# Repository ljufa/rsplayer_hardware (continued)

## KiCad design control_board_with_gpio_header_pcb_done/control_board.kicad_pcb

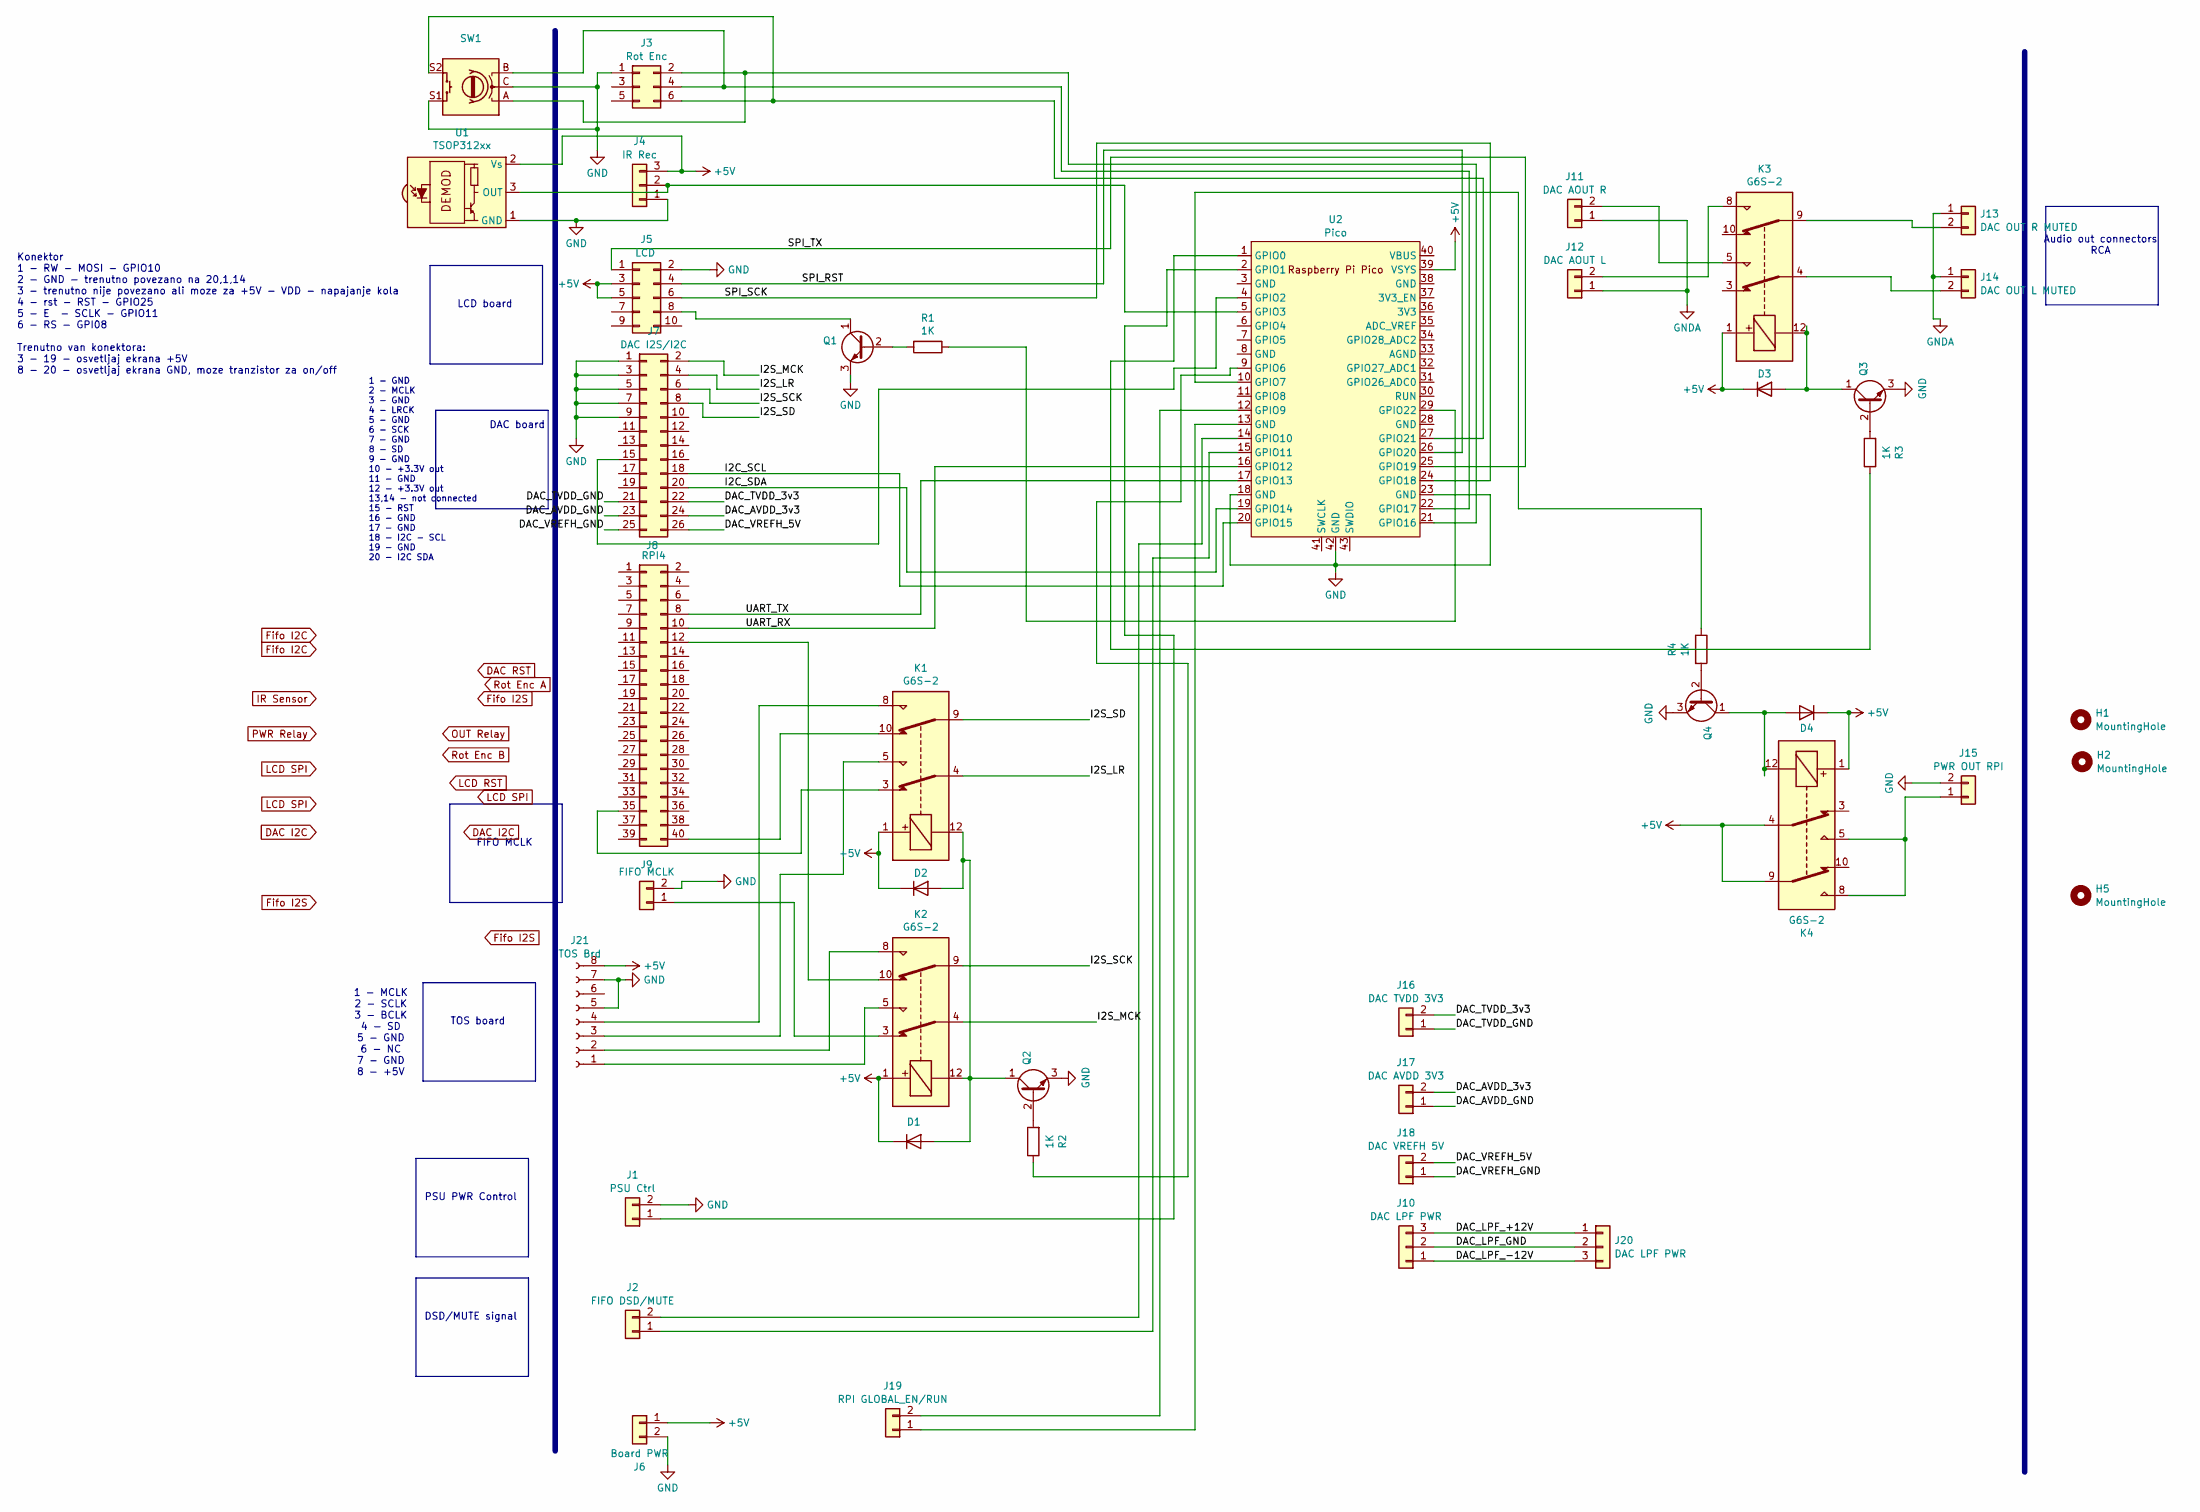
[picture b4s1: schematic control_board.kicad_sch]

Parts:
D1, D2, D3, D4: 1N4004; D_MELF
H1, H2, H5: MountingHole; MountingHole_3.2mm_M3
J1: PSU Ctrl; PinHeader_1x02_P2.54mm_Vertical
J2: FIFO DSD/MUTE; PinHeader_1x02_P2.54mm_Vertical
J3: Rot Enc; IDC-Header_2x03_P2.54mm_Vertical
J4: IR Rec; PinHeader_1x03_P2.54mm_Vertical
J5: LCD; IDC-Header_2x05_P2.54mm_Vertical
J6: Board PWR; TerminalBlock_Philmore_TB132_1x02_P5.00mm_Horizontal
J7: DAC I2S/I2C; diyinkhak4497board
J8: RPI4; PinHeader_2x20_P2.54mm_Vertical
J9: FIFO MCLK; PinHeader_1x02_P2.54mm_Vertical
J10: DAC LPF PWR; TerminalBlock_Philmore_TB133_1x03_P5.00mm_Horizontal
J11: DAC AOUT R; PinHeader_1x02_P2.54mm_Vertical
J12: DAC AOUT L; PinHeader_1x02_P2.54mm_Vertical
J13: DAC OUT R MUTED; PinHeader_1x02_P2.54mm_Vertical
J14: DAC OUT L MUTED; PinHeader_1x02_P2.54mm_Vertical
J15: PWR OUT RPI; TerminalBlock_Philmore_TB132_1x02_P5.00mm_Horizontal
J16: DAC TVDD 3V3; TerminalBlock_Philmore_TB132_1x02_P5.00mm_Horizontal
J17: DAC AVDD 3V3; TerminalBlock_Philmore_TB132_1x02_P5.00mm_Horizontal
J18: DAC VREFH 5V; TerminalBlock_Philmore_TB132_1x02_P5.00mm_Horizontal
J19: RPI GLOBAL_EN/RUN; PinHeader_1x02_P2.54mm_Vertical
J20: DAC LPF PWR; PinSocket_1x03_P2.54mm_Vertical
J21: TOS Brd; tosInputBoard
K1, K2, K3, K4: G6S-2; Relay_DPDT_Omron_G6S-2
Q1, Q2, Q3, Q4: BC547; TO-92_Inline
R1, R2, R3, R4: 1K; R_1206_3216Metric_Pad1.30x1.75mm_HandSolder
SW1: RotaryEncoder_Switch
U1: TSOP312xx; Vishay_CAST-3Pin
U2: Pico; RaspberryPi_Pico_Common_THT

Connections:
+5V: D1.1 (K), D2.1 (K), D3.1 (K), D4.1 (K), J4.3, J5.3, J5.5, J6.1, J21.8, K1.1, K2.1, K3.1, K4.1, K4.4, K4.9, U2.39 (VSYS)
/DAC_AVDD_3v3: J7.24, J17.2
/DAC_AVDD_GND: J7.23, J17.1
/DAC_LPF_+12V: J10.3, J20.1
/DAC_LPF_-12V: J10.1, J20.3
/DAC_LPF_GND: J10.2, J20.2
/DAC_TVDD_3v3: J7.22, J16.2
/DAC_TVDD_GND: J7.21, J16.1
/DAC_VREFH_5V: J7.26, J18.2
/DAC_VREFH_GND: J7.25, J18.1
/I2C_SCL: J7.18, U2.20 (GPIO15)
/I2C_SDA: J7.20, U2.19 (GPIO14)
/I2S_LR: J7.4, K1.4
/I2S_MCK: J7.2, K2.4
/I2S_SCK: J7.6, K2.9
/I2S_SD: J7.8, K1.9
/SPI_RST: J5.4, U2.26 (GPIO20)
/SPI_SCK: J5.6, U2.24 (GPIO18)
/SPI_TX: J5.1, U2.25 (GPIO19)
/UART_RX: J8.10, U2.16 (GPIO12)
/UART_TX: J8.8, U2.17 (GPIO13)
GND: J1.2, J3.1, J4.1, J5.2, J6.2, J7.1, J7.3, J7.5, J7.7, J7.9, J9.2, J15.2, J21.5, J21.7, Q1.3 (E), Q2.3 (E), Q3.3 (E), Q4.3 (E), U2.18 (GND), U2.23 (GND), U2.42 (GND)
GNDA: J11.1, J12.1, J13.1, J14.1
unnamed: D1.2 (A), D2.2 (A), K1.12, K2.12, Q2.1 (C)
unnamed: D3.2 (A), K3.12, Q3.1 (C)
unnamed: D4.2 (A), K4.12, Q4.1 (C)
unnamed: J1.1, U2.2 (GPIO1)
unnamed: J2.1, U2.15 (GPIO11)
unnamed: J2.2, U2.14 (GPIO10)
unnamed: J3.2, U2.21 (GPIO16)
unnamed: J3.4, U2.22 (GPIO17)
unnamed: J3.6, U2.27 (GPIO21)
unnamed: J4.2, U2.5 (GPIO3)
unnamed: J5.8, Q1.1 (C)
unnamed: J7.15, U2.4 (GPIO2)
unnamed: J8.12, K2.10
unnamed: J8.35, K1.3
unnamed: J8.40, K1.10
unnamed: J9.1, K2.3
unnamed: J11.2, K3.5
unnamed: J12.2, K3.8
unnamed: J13.2, K3.9
unnamed: J14.2, K3.4
unnamed: J15.1, K4.5, K4.8
unnamed: J19.1, U2.13 (GND)
unnamed: J19.2, U2.12 (GPIO9)
unnamed: J21.1, K2.5
unnamed: J21.2, K2.8
unnamed: J21.3, K1.5
unnamed: J21.4, K1.8
unnamed: Q1.2 (B), R1.2
unnamed: Q2.2 (B), R2.2
unnamed: Q3.2 (B), R3.2
unnamed: Q4.2 (B), R4.2
unnamed: R3.1, U2.1 (GPIO0)
unnamed: R2.1, U2.9 (GPIO6)
unnamed: R4.1, U2.10 (GPIO7)
unnamed: R1.1, U2.29 (GPIO22)

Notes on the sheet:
FIFO MCLK
Audio out connectors RCA
Konektor 1 - RW - MOSI - GPIO10 2 - GND - trenutno povezano na 20,1,14 3 - trenutno nije povezano ali moze za +5V - VDD - napajanje kola 4 - rst - RST - GPIO25 5 - E - SCLK - GPIO11 6 - RS - GPI08 Trenutno van konektora: 3 - 19 - osvetljaj ekrana +5V 8 - 20 - osvetljaj ekrana GND, moze tranzistor z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
DAC board
LCD board
PSU PWR Control
DSD/MUTE signal
1 - GND 2 - MCLK 3 - GND 4 - LRCK 5 - GND 6 - SCK 7 - GND 8 - SD 9 - GND 10 - +3.3V out 11 - GND 12 - +3.3V out 13,14 - not connected 15 - RST 16 - GND 17 - GND 18 - I2C - SCL 19 - GND 20 - I2C SDA
1 - MCLK 2 - SCLK 3 - BCLK 4 - SD 5 - GND 6 - NC 7 - GND 8 - +5V
TOS board

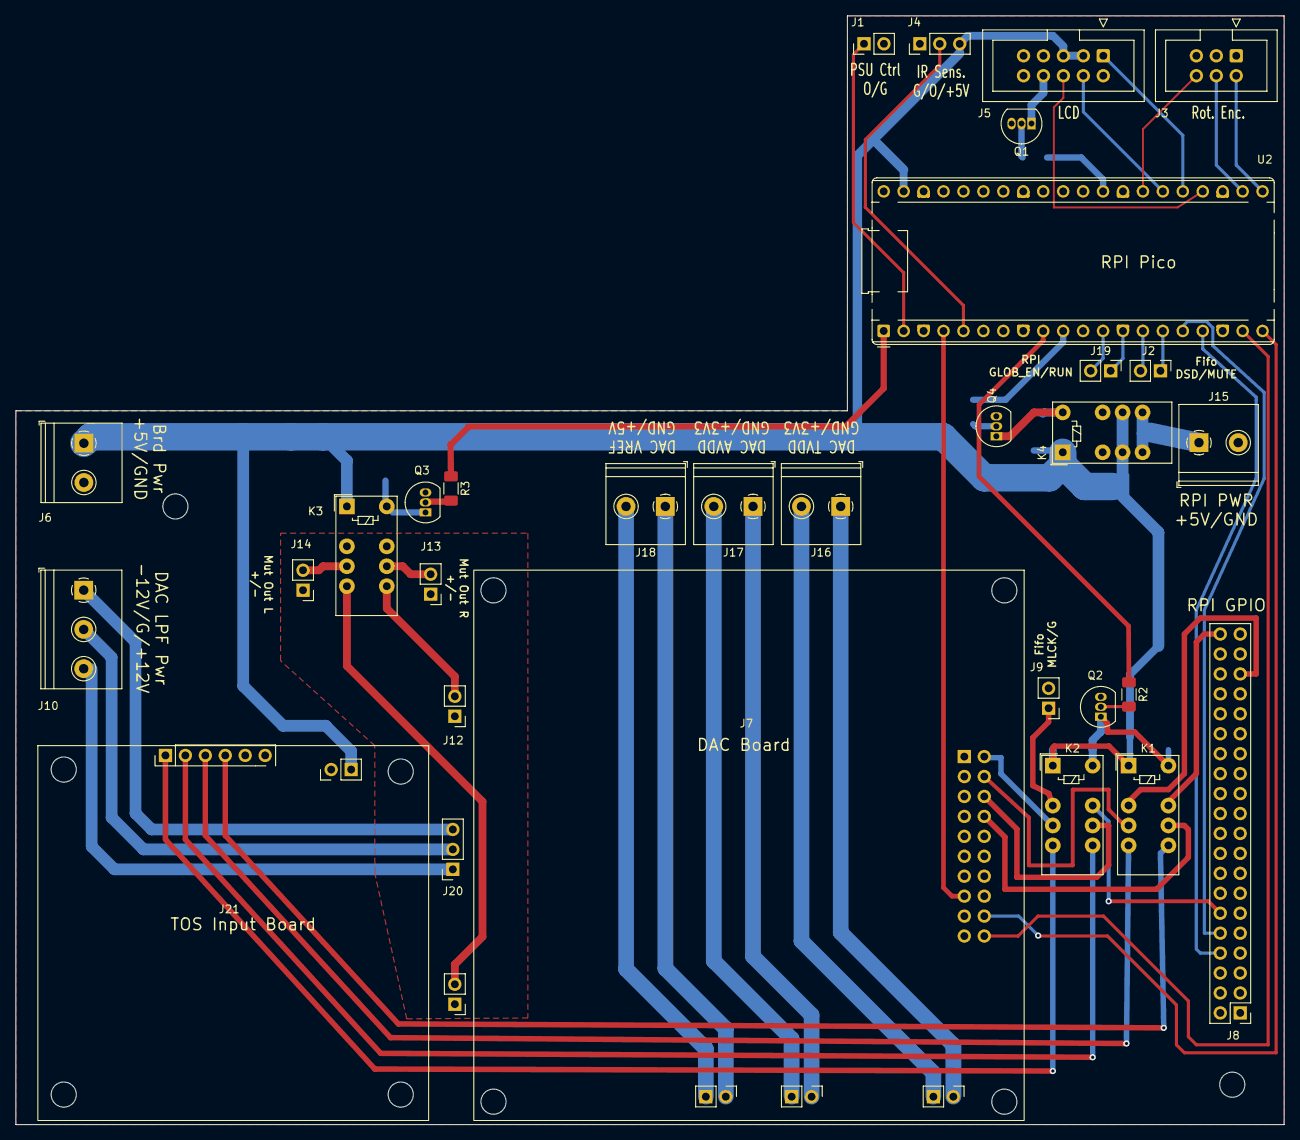
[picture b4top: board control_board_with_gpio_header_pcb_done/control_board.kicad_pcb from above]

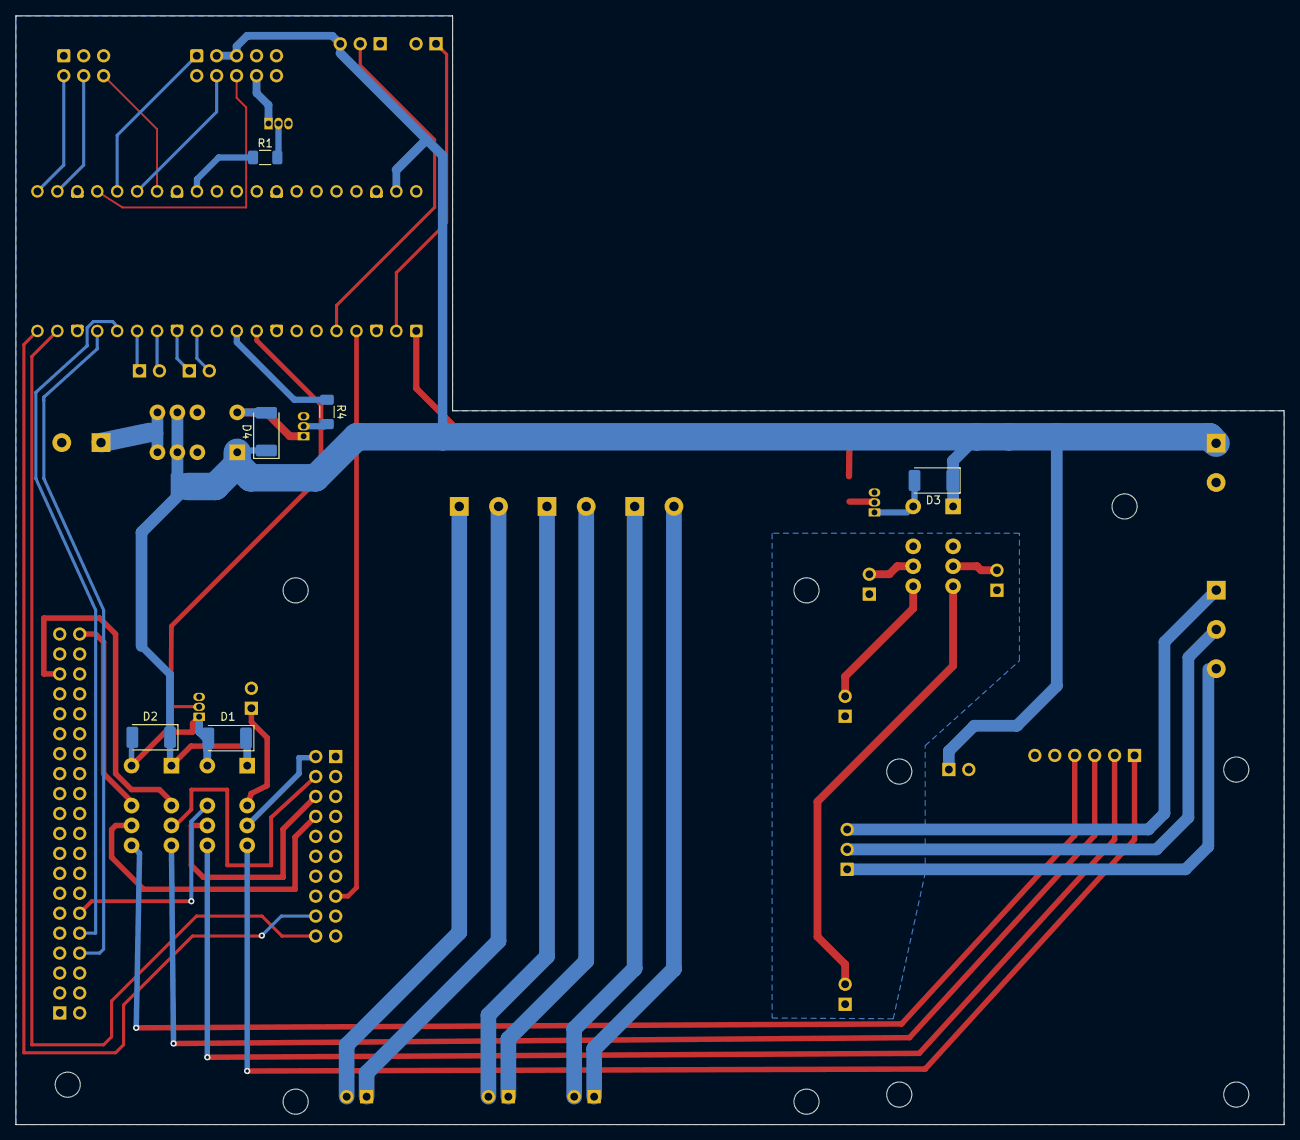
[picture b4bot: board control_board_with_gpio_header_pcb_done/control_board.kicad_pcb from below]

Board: 2 copper layers, 161.5 x 141.2 mm, 41 parts (6 on the bottom side), 58 nets.

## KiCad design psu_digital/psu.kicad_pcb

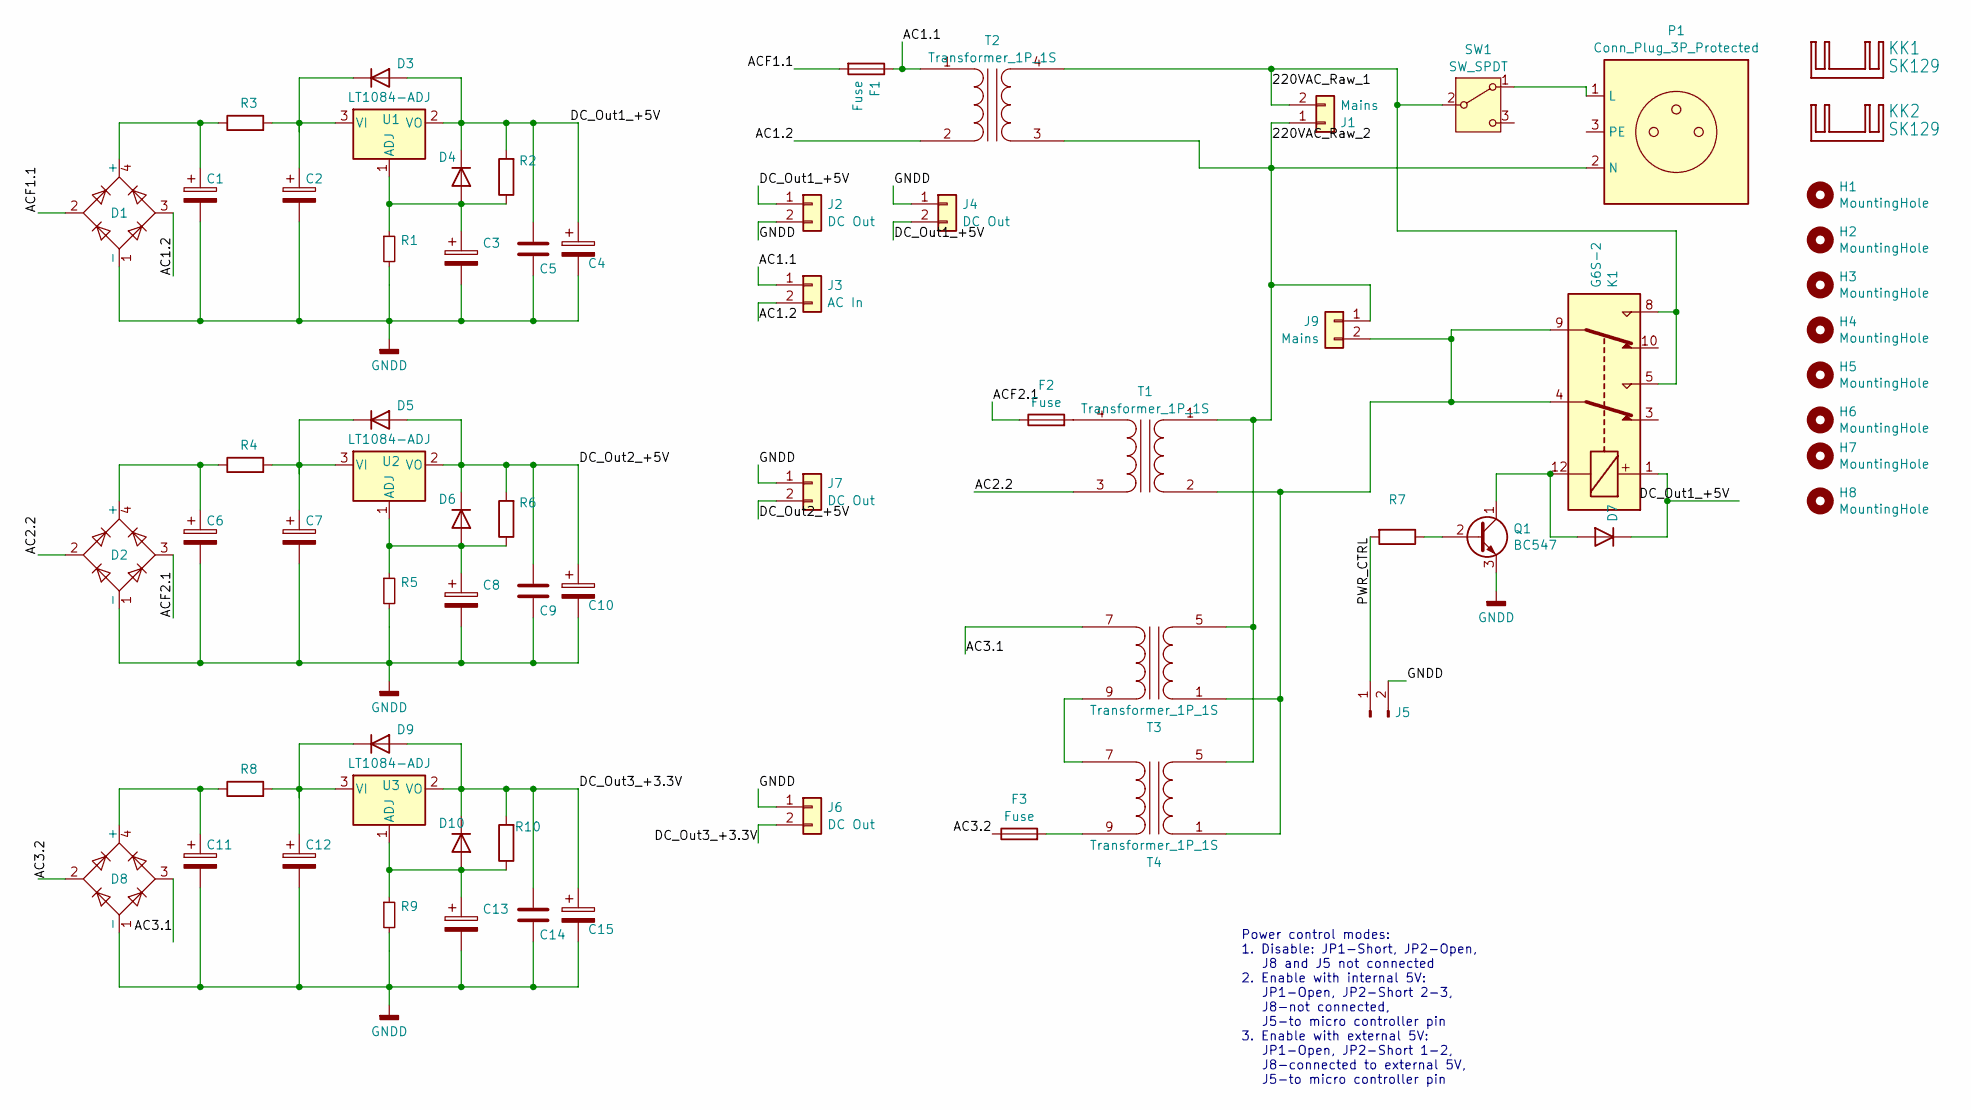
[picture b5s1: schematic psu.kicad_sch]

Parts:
C1, C2: 2200uF/40v; CP_Axial_L42.0mm_D26.0mm_P45.00mm_Horizontal
C3, C8, C13: 10uF/35V; CP_Radial_D5.0mm_P2.00mm
C4, C10, C15: 220uF; CP_Radial_D10.0mm_P5.00mm
C5, C9, C14: 1uF; C_Rect_L10.0mm_W2.5mm_P7.50mm_MKS4
C6, C7, C11, C12: 2200uF/40v; CP_Radial_D13.0mm_P5.00mm
D1, D2, D8: B80C3x00-2200A; Diode_Bridge_32.0x5.6x17.0mm_P10.0mm_P7.5mm
D3, D4, D5, D6, D9, D10: 1N4004; D_DO-41_SOD81_P10.16mm_Horizontal
D7: 1N4004; D_A-405_P7.62mm_Horizontal
F1, F2, F3: Fuse; SH22,5A
H1, H2, H5, H6, H7, H8: MountingHole; MountingHole_3.2mm_M3
H3, H4: MountingHole; MountingHole_3.2mm_M3_Pad_Via
J1, J9: Mains; TerminalBlock_Philmore_TB132_1x02_P5.00mm_Horizontal
J2, J4, J6, J7: DC Out; TerminalBlock_Philmore_TB132_1x02_P5.00mm_Horizontal
J3: AC In; TerminalBlock_Philmore_TB132_1x02_P5.00mm_Horizontal
J5: Conn_01x02_Pin; JST_EH_B2B-EH-A_1x02_P2.50mm_Vertical
K1: G6S-2; Relay_DPDT_Omron_G6S-2
KK1, KK2: SK129; Heatsink_Fischer_SK104-STCB_35x13mm__2xDrill3.5mm_ScrewM3
P1: Conn_Plug_3P_Protected
Q1: BC547; TO-92_Inline
R1, R5, R9: 82R; R_Axial_DIN0207_L6.3mm_D2.5mm_P10.16mm_Horizontal
R2, R6, R10: 330; R_Axial_DIN0207_L6.3mm_D2.5mm_P10.16mm_Horizontal
R3, R4, R8: 2.2; R_Axial_DIN0617_L17.0mm_D6.0mm_P20.32mm_Horizontal
R7: 1k; R_Axial_DIN0207_L6.3mm_D2.5mm_P2.54mm_Vertical
SW1: SW_SPDT
T1: Transformer_1P_1S; MYRRA_44266
T2: Transformer_1P_1S
T3, T4: Transformer_1P_1S; Transformer_Breve_TEZ-35x42_crni_6v_3.va
U1, U2, U3: LT1084-ADJ; TO-220-3_Vertical

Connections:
/220VAC_Raw_1: J1.2, K1.5, K1.8, SW1.2 (B), T2.4 (SB)
/220VAC_Raw_2: J1.1, J9.1, P1.2 (N), T1.1 (AA), T2.3 (SA), T3.5 (AB), T4.5 (AB)
/AC1.1: F1.1, J3.1, T2.1 (AA)
/AC1.2: D1.3, J3.2, T2.2 (AB)
/AC2.2: D2.2, T1.3 (SA)
/AC3.1: D8.3, T3.7 (SA)
/AC3.2: D8.2, F3.1
/ACF1.1: D1.2, F1.2
/ACF2.1: D2.3, F2.1
/DC_Out1_+5V: C4.1, C5.1, D3.2 (A), D4.1 (K), D7.1 (K), J2.1, J4.2, K1.1, R2.2, U1.2 (VO)
/DC_Out2_+5V: C9.1, C10.1, D5.2 (A), D6.1 (K), J7.2, R6.2, U2.2 (VO)
/DC_Out3_+3.3V: C14.1, C15.1, D9.2 (A), D10.1 (K), J6.2, R10.2, U3.2 (VO)
/PWR_CTRL: J5.1, R7.2
GNDD: C1.2, C2.2, C3.2, C4.2, C5.2, C6.2, C7.2, C8.2, C9.2, C10.2, C11.2, C12.2, C13.2, C14.2, C15.2, D1.1 (-), D2.1 (-), D8.1 (-), J2.2, J4.1, J5.2, J6.1, J7.1, Q1.3 (E), R1.2, R5.2, R9.2
unnamed 14: C1.1, D1.4 (+), R3.1; also elsewhere on the board
unnamed: C6.1, D2.4 (+), R4.1
unnamed 16: C2.1, D3.1 (K), R3.2, U1.3 (VI); also elsewhere on the board
unnamed: C3.1, D4.2 (A), R1.1, R2.1, U1.1 (ADJ)
unnamed: C7.1, D5.1 (K), R4.2, U2.3 (VI)
unnamed: C8.1, D6.2 (A), R5.1, R6.1, U2.1 (ADJ)
unnamed: D7.2 (A), K1.12, Q1.1 (C)
unnamed: C11.1, D8.4 (+), R8.1
unnamed: C12.1, D9.1 (K), R8.2, U3.3 (VI)
unnamed: C13.1, D10.2 (A), R9.1, R10.1, U3.1 (ADJ)
unnamed: J9.2, K1.4, K1.9, T1.2 (AB), T3.1 (AA), T4.1 (AA)
unnamed: P1.1 (L), SW1.1 (A)
unnamed: Q1.2 (B), R7.1
unnamed: F2.2, T1.4 (SB)
unnamed: T3.9 (SB), T4.7 (SA)
unnamed: F3.2, T4.9 (SB)

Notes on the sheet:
Power control modes: 1. Disable: JP1-Short, JP2-Open, J8 and J5 not connected 2. Enable with internal 5V: JP1-Open, JP2-Short 2-3, J8-not connected, J5-to micro controller pin 3. Enable with external 5V: JP1-Open, JP2-Short 1-2, J8-connected to external 5V, J5-to micro controller pin

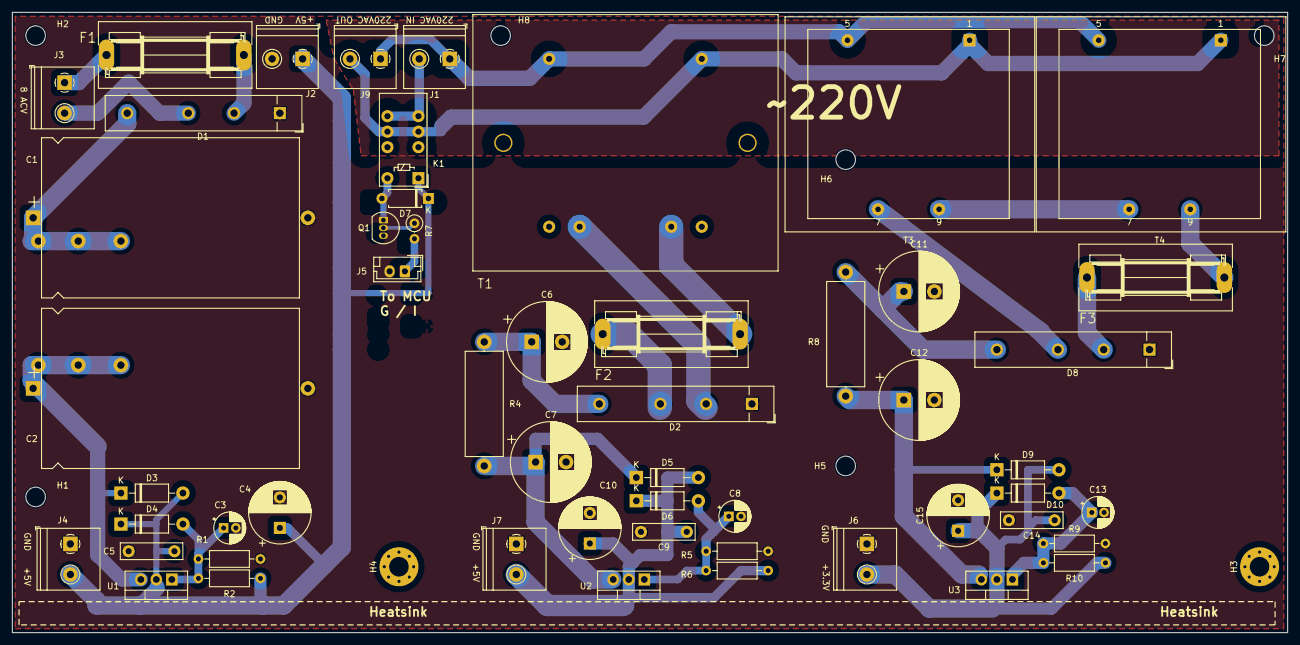
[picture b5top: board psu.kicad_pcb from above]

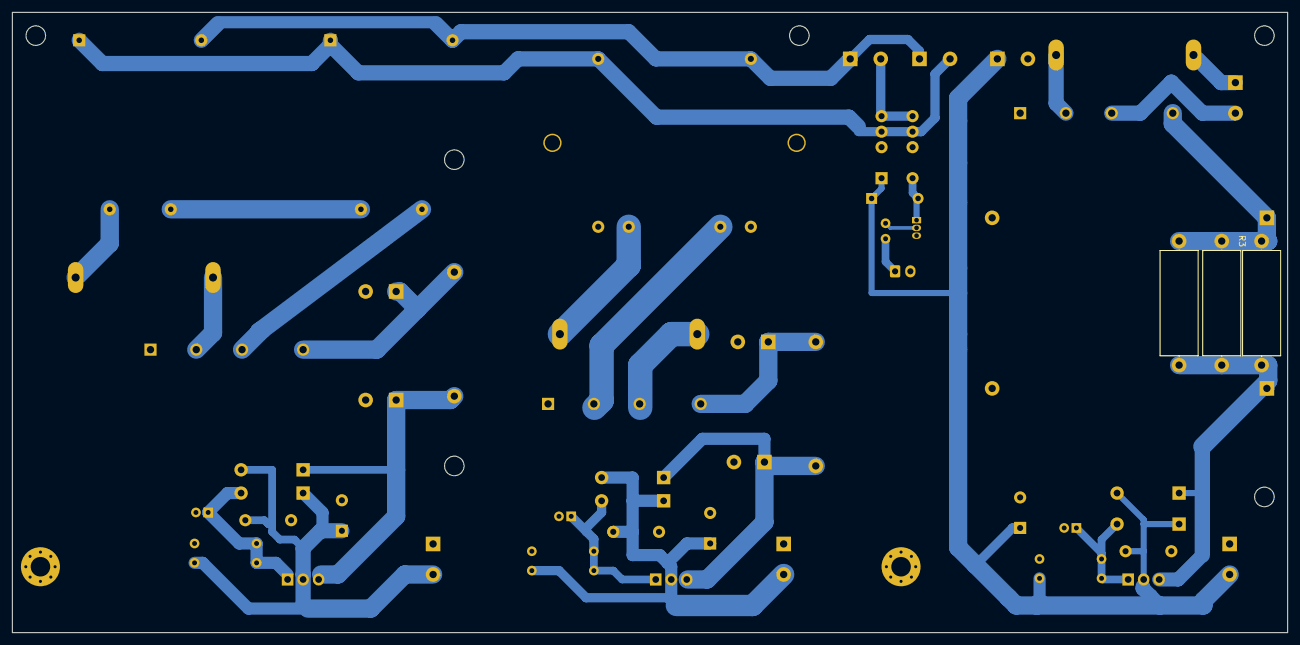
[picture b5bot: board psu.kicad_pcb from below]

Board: 2 copper layers, 208.9 x 101.6 mm, 64 parts (3 on the bottom side), 29 nets.

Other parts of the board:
R3#2, R3#3: 2.2; R_Axial_DIN0617_L17.0mm_D6.0mm_P20.32mm_Horizontal

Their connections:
unnamed 14: R3#2.1, R3#3.1; also elsewhere on the board
unnamed 16: R3#2.2, R3#3.2; also elsewhere on the board

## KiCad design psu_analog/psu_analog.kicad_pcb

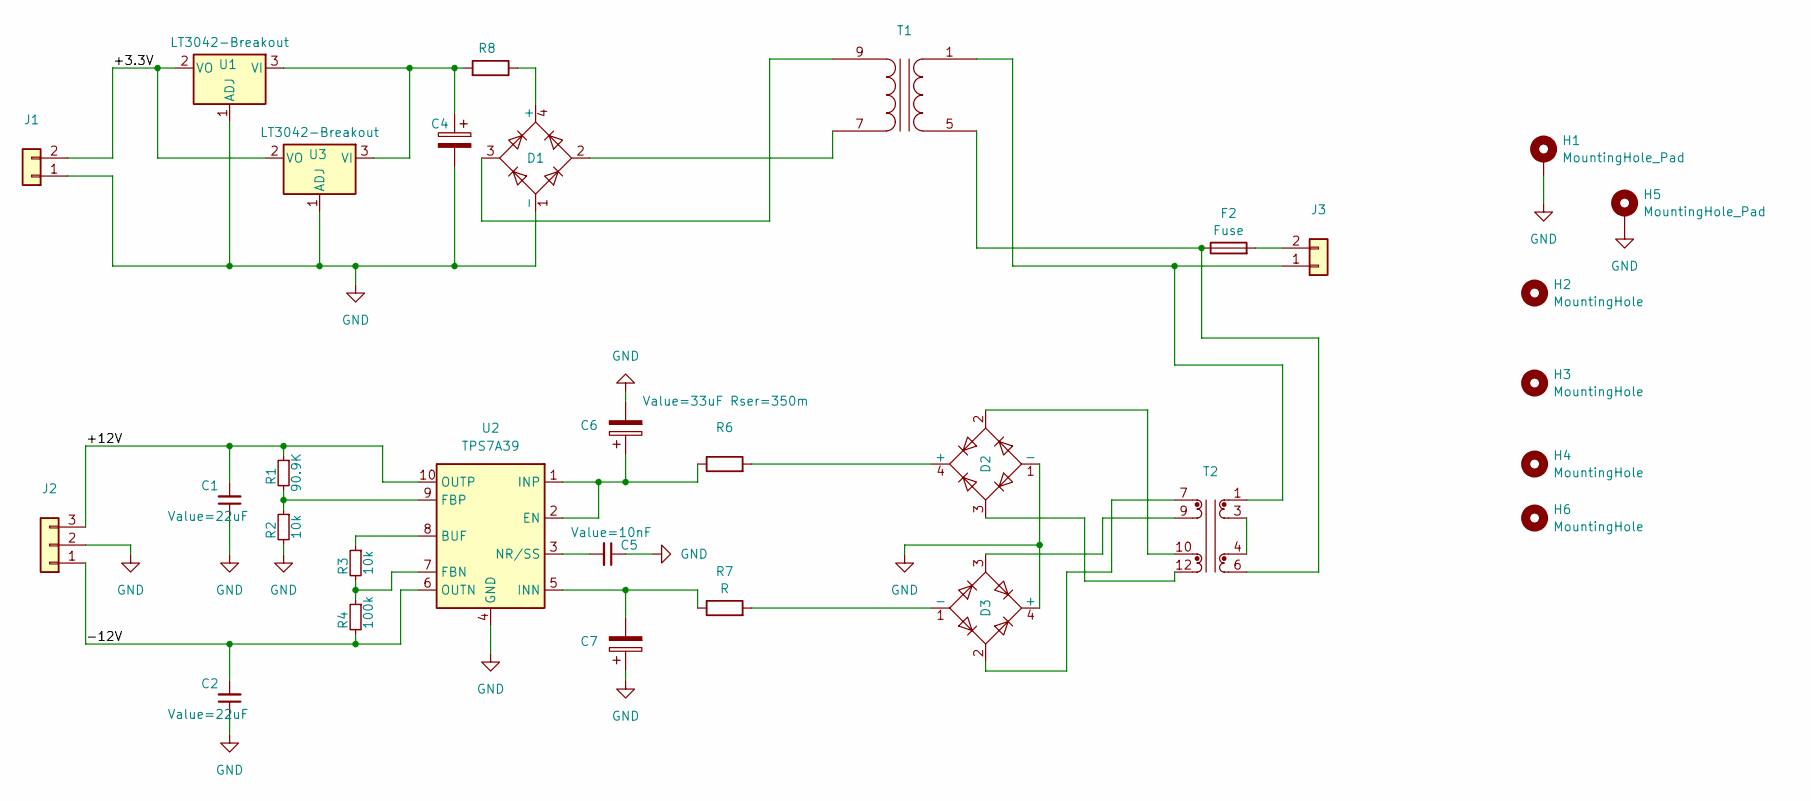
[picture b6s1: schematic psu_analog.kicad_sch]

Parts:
C1, C2: Value=22uF; C_1206_3216Metric_Pad1.33x1.80mm_HandSolder
C4: 2200uF/40v; CP_Radial_D13.0mm_P5.00mm
C5: Value=10nF; C_0603_1608Metric_Pad1.08x0.95mm_HandSolder
C6, C7: Value=33uF Rser=350m; CP_EIA-3528-21_Kemet-B_Pad1.50x2.35mm_HandSolder
D1, D2, D3: B80C3x00-2200A; diode_bridge_round
F2: Fuse; SH22,5A
H1, H5: MountingHole_Pad; MountingHole_2.2mm_M2_Pad_Via
H2, H3, H6: MountingHole; MountingHole_2.2mm_M2
H4: MountingHole; MountingHole_2.2mm_M2_Pad_Via
J1, J3: DC Out; TerminalBlock_Philmore_TB132_1x02_P5.00mm_Horizontal
J2: Conn_01x03; TerminalBlock_Philmore_TB133_1x03_P5.00mm_Horizontal
R1: 90.9K; R_0603_1608Metric_Pad0.98x0.95mm_HandSolder
R2, R3: 10k; R_0603_1608Metric_Pad0.98x0.95mm_HandSolder
R4: 100k; R_0603_1608Metric_Pad0.98x0.95mm_HandSolder
R6, R7: R; R_Axial_DIN0411_L9.9mm_D3.6mm_P15.24mm_Horizontal
R8: 2.2; R_Axial_DIN0411_L9.9mm_D3.6mm_P15.24mm_Horizontal
T1: Transformer_1P_1S; Transformer_Breve_TEZ-35x42_crni_6v_3.va
T2: Murata_PL10-28-130B; Transformer_Murata_PL10-28-130B
U1, U3: LT3042-Breakout; TO-220-3_Vertical
U2: TPS7A39; Texas_S-PVSON-N10_ThermalVias

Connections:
/+3.3V: J1.2, U1.2 (VO), U3.2 (VO)
/+12V: C1.2, J2.3, R1.1, U2.10 (OUTP)
/-12V: C2.2, J2.1, R4.2, U2.6 (OUTN)
GND: C1.1, C2.1, C4.2, C5.1, C6.2, C7.1, D1.1 (-), D2.1 (-), D3.4 (+), H1.1, H5.1, J1.1, J2.2, R2.2, U1.1 (ADJ), U2.4 (GND), U2.11 (GND), U3.1 (ADJ)
unnamed: D1.4 (+), R8.1
unnamed: D2.4 (+), R6.2
unnamed: D2.2, T2.10
unnamed: D2.3, T2.12
unnamed: D3.1 (-), R7.2
unnamed: D3.2, T2.7
unnamed: D3.3, T2.9
unnamed: J3.1, T1.1 (AA), T2.1
unnamed: F2.2, J3.2
unnamed: F2.1, T1.5 (AB), T2.6
unnamed: D1.2, T1.7 (SA)
unnamed: D1.3, T1.9 (SB)
unnamed: T2.3, T2.4
unnamed: C4.1, R8.2, U1.3 (VI), U3.3 (VI)
unnamed: R3.1, U2.8 (BUF)
unnamed: C6.1, R6.1, U2.1 (INP), U2.2 (EN)
unnamed: R3.2, R4.1, U2.7 (FBN)
unnamed: R1.2, R2.1, U2.9 (FBP)
unnamed: C7.2, R7.1, U2.5 (INN)
unnamed: C5.2, U2.3 (NR/SS)

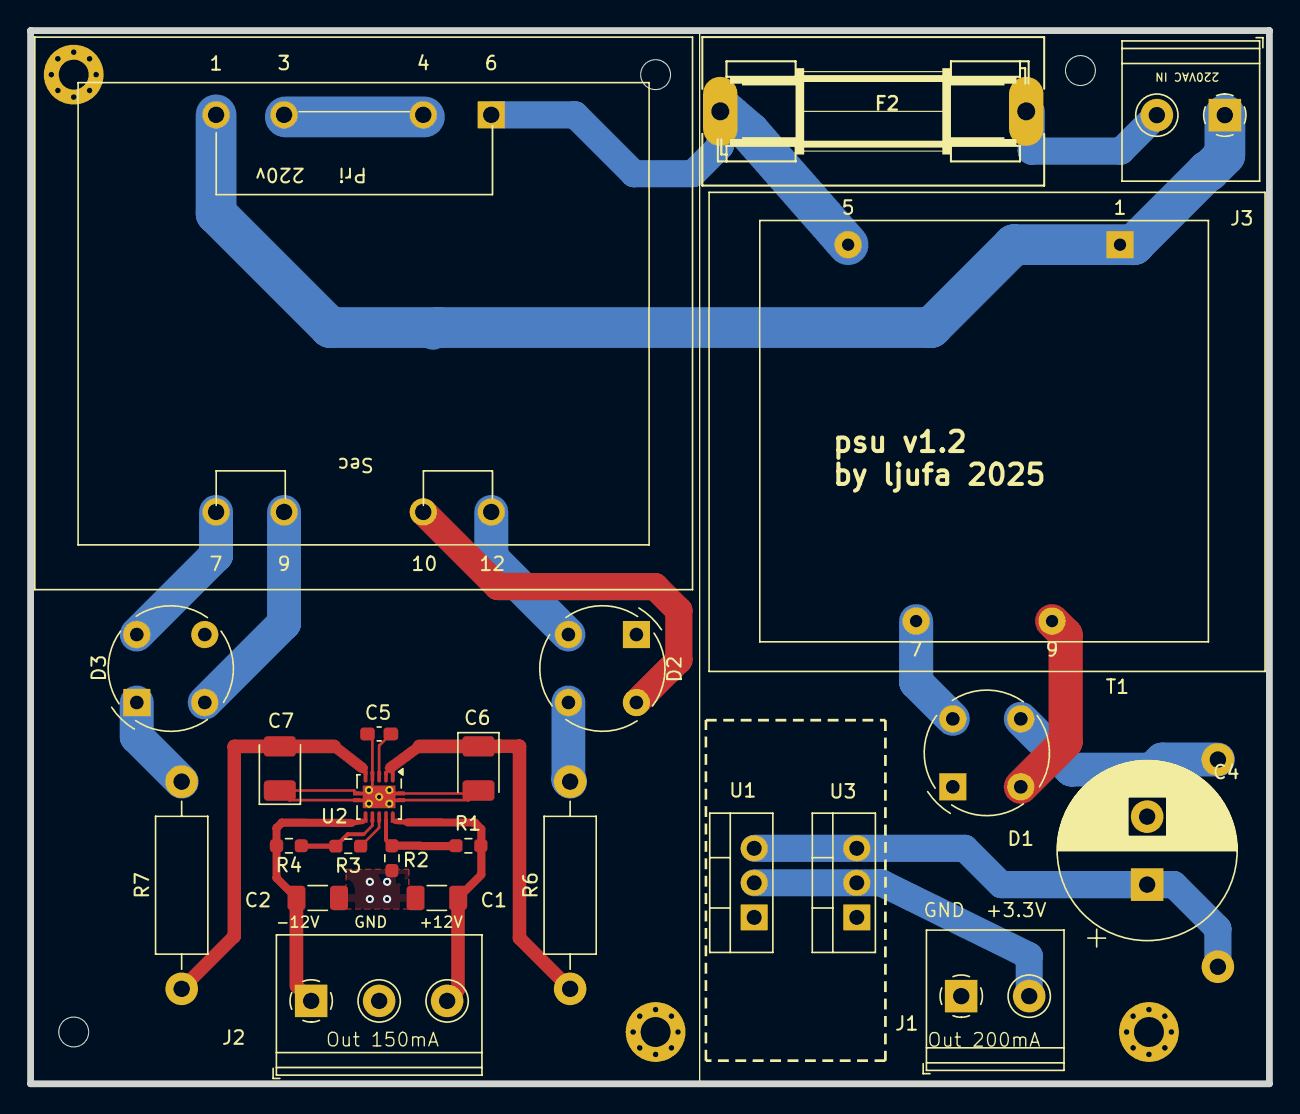
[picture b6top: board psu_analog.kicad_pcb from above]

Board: 2 copper layers, 91.1 x 77.5 mm, 31 parts (1 on the bottom side), 24 nets.

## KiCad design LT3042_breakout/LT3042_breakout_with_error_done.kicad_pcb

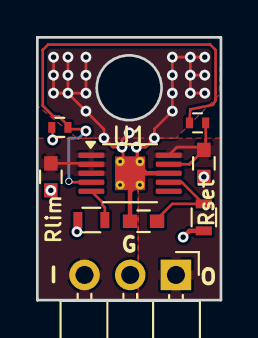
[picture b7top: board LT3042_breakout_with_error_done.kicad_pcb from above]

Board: 2 copper layers, 10.2 x 14.6 mm, 10 parts (0 on the bottom side), 7 nets.

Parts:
C1, C2, C3: 10u; C_0603
J1: CONN_01X03; Pin_Header_Angled_1x03_Pitch2.54mm
R1: 33.2K; R_0603
R2: 300; R_0603
R3: 200k; R_0402
R4: 5.6k; R_0402
U1: LT3045EDD; MSOP-10-1EP_3x3mm_P0.5mm_EP1.68x1.88mm_ThermalVias
W1: NET-TIE; NET-TIE-0.15mm

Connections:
/in: C1.1, J1.3, U1.1 (IN), U1.2 (IN), U1.3 (EN/UV)
/out: C3.1, J1.1, R3.1, U1.10 (OUT), W1.1
GND: C1.2, C2.2, C3.2, J1.2, R1.2, R2.2, R4.2, U1.8 (GND), U1.11
unnamed: R2.1, U1.5 (ILIM)
unnamed: U1.9 (OUTS), W1.2
unnamed: R3.2, R4.1, U1.4 (PG)
unnamed: C2.1, R1.1, U1.7 (SET)

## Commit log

2025-10-02 Create LICENSE
2025-10-02 import
2025-10-02 add readme
2025-12-24 v2 board
2026-01-08 add gerber and bom files
2026-01-08 add missing images
2026-01-08 fix lt3042 breakout
